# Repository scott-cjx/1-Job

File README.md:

# Overview

`1 Job` is a Custom Designed PCB by [Scott CJX](https://scott-cjx.github.io) for [Nanyang Venture Formula NVF](https://nanyang-venture-formula.github.io/). Since its designer is a software person, `1 Job` is created to follow the principle of programming, having only `1 Job`.

As this PCB is designed to have `1 Job`, you may then wonder what is that `1 Job`. Well it is meant to be one of many nodes in a CanBus network. Its job is to act as either an [Input](#input) or [Output](#output) node. More will be explained.

#### You might want to see:

- [Brain](https://scott-cjx.github.io/brain) - `1 Job's` partner-in-crime
- [NVF-Data Acquisition](https://nanyang-venture-formula.github.io/) - how `1 Job` and `Brain` would work together to form a comprehensive Car EE System.

## Other Documentations

- [Software](./software)
- [Hardware](./hardware)
- [Production](./production)

## Input

An Input node is one that will take in a user input or sensor interface and transmit its reading to the CanBus network. Some sensors that `1 Job` interfaces with include:

- (Analog) Potentiometer
- (Digital) Push Button/ Switch

The standard program flow of an Input node will be as follows:

``` mermaid
flowchart TD
    A[Setup] --> B(Loop)
    B --> C(Read sensor value)
    C --> D(Process sensor value)
    D --> E(Transmit processed \nvalues via CanBus)
    E --> B
```

## Output

An Output node is one that will poll the CanBus network for instructions, pulling a pin high/low as per required. Furthermore, `1 Job` will be equipped with a Solid State Relay, allowing it to connect/ disconnect a circuit much like a programmable switch, but without the need of connecting the circuits together. 

The standard program flow of an Output node will be as follows:

1. Poll for instructions from `brain` nodes
2. Pull pin high/low as per instructed

``` mermaid
flowchart TD
    A[Setup] --> B(Loop)
    B --> C(Wait for CanBus Message)
    C --> D(Read CanBus Instructions)
    D --> E(Drive Pin high/low \nas per instructions)
    E --> B
```

## Preview

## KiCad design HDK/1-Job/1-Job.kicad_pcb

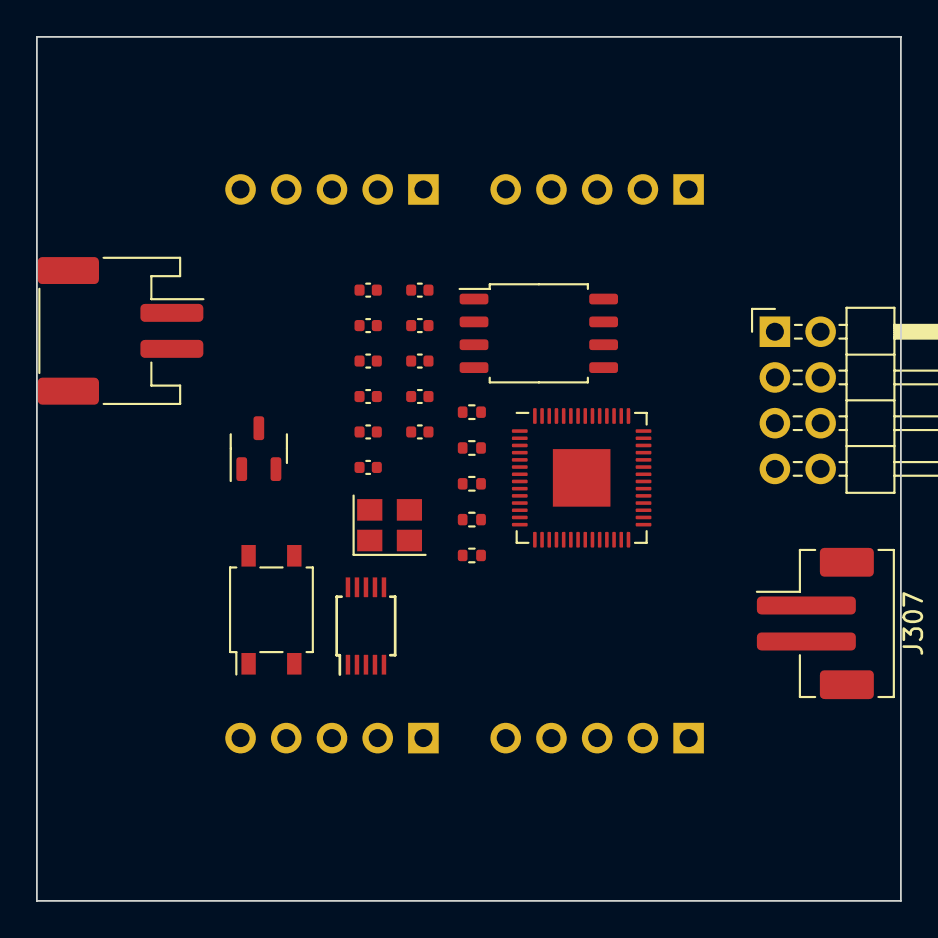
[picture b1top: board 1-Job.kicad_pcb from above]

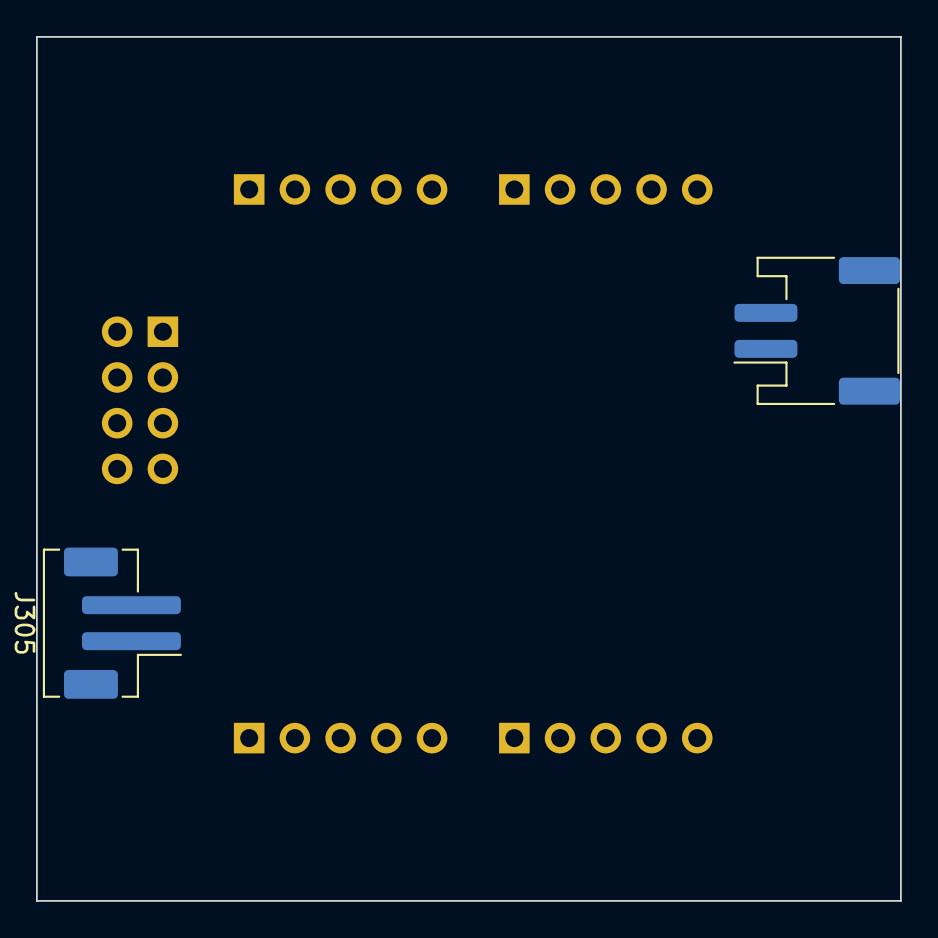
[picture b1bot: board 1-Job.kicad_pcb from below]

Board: 2 copper layers, 48.0 x 48.0 mm, 26 parts (2 on the bottom side), 20 nets, no tracks yet.

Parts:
C201, C202, C203, C204, C205, C206, C207, C208, C209: 100n; C_0402_1005Metric
C210, C211: 10p; C_0402_1005Metric
J301, J303: Can Conn; JST_PH_S2B-PH-SM4-TB_1x02-1MP_P2.00mm_Horizontal
J305, J307: Can Conn; JST_PH_B2B-PH-SM4-TB_1x02-1MP_P2.00mm_Vertical
R201, R205: 1K; R_0402_1005Metric
R202, R203: 27; R_0402_1005Metric
R204: 1K (NC); R_0402_1005Metric
U201: W25Q128JVS; SOIC-8_5.23x5.23mm_P1.27mm
U202: RP2040; QFN-56-1EP_7x7mm_P0.4mm_EP3.2x3.2mm
U401: ADS1015IDGS; TSSOP-10_3x3mm_P0.5mm
U402: ASSR-1218; SO-4_4.4x4.3mm_P2.54mm
U501: LR7533-T LR; SOT-23-3
Y201: 12 MHz; Crystal_SMD_3225-4Pin_3.2x2.5mm

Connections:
+1V1: C208.1, C209.1, U202.23 (DVDD), U202.45 (VREG_VOUT), U202.50 (DVDD)
+3V3: C201.1, C202.1, C203.1, C204.1, C205.1, C206.1, C207.1, R204.1, U201.8 (VCC), U202.1 (IOVDD), U202.10 (IOVDD), U202.22 (IOVDD), U202.33 (IOVDD), U202.42 (IOVDD), U202.43 (ADC_AVDD), U202.44 (VREG_IN), U202.48 (USB_VDD), U202.49 (IOVDD), U401.8 (VDD), U501.2 (VO)
/Connectors/CAN1_H: J301.2, J303.2
/Connectors/CAN1_L: J301.1, J303.1
/Connectors/CAN2_H: J305.2, J307.2
/Connectors/CAN2_L: J305.1, J307.1
/Controller/HSE_IN: C210.1, U202.20 (XIN), Y201.1
/Controller/HSE_OUT: C211.1, R205.1, Y201.3
/Controller/QSPI_SCLK: U201.6 (CLK), U202.52 (QSPI_SCLK)
/Controller/QSPI_SD0: U201.5 (DI(IO0)), U202.53 (QSPI_SD0)
/Controller/QSPI_SD1: U201.2 (DO(IO1)), U202.55 (QSPI_SD1)
/Controller/QSPI_SD2: U201.3 (IO2), U202.54 (QSPI_SD2)
/Controller/QSPI_SD3: U201.7 (IO3), U202.51 (QSPI_SD3)
/Controller/QSPI_SS: R201.1, R204.2, U201.1 (~CS), U202.56 (QSPI_SS)
/I2C0_SCL: U202.12 (GPIO9), U401.10 (SCL)
/I2C0_SDA: U202.11 (GPIO8), U401.9 (SDA)
GND: C201.2, C202.2, C203.2, C204.2, C205.2, C206.2, C207.2, C208.2, C209.2, C210.2, C211.2, U201.4 (GND), U202.19 (TESTEN), U202.57 (GND), U401.1 (ADDR), U401.3 (GND), U402.2, U501.1 (GND), Y201.2, Y201.4
unnamed: R203.2, U202.46 (USB_DM)
unnamed: R202.2, U202.47 (USB_DP)
unnamed: R205.2, U202.21 (XOUT)

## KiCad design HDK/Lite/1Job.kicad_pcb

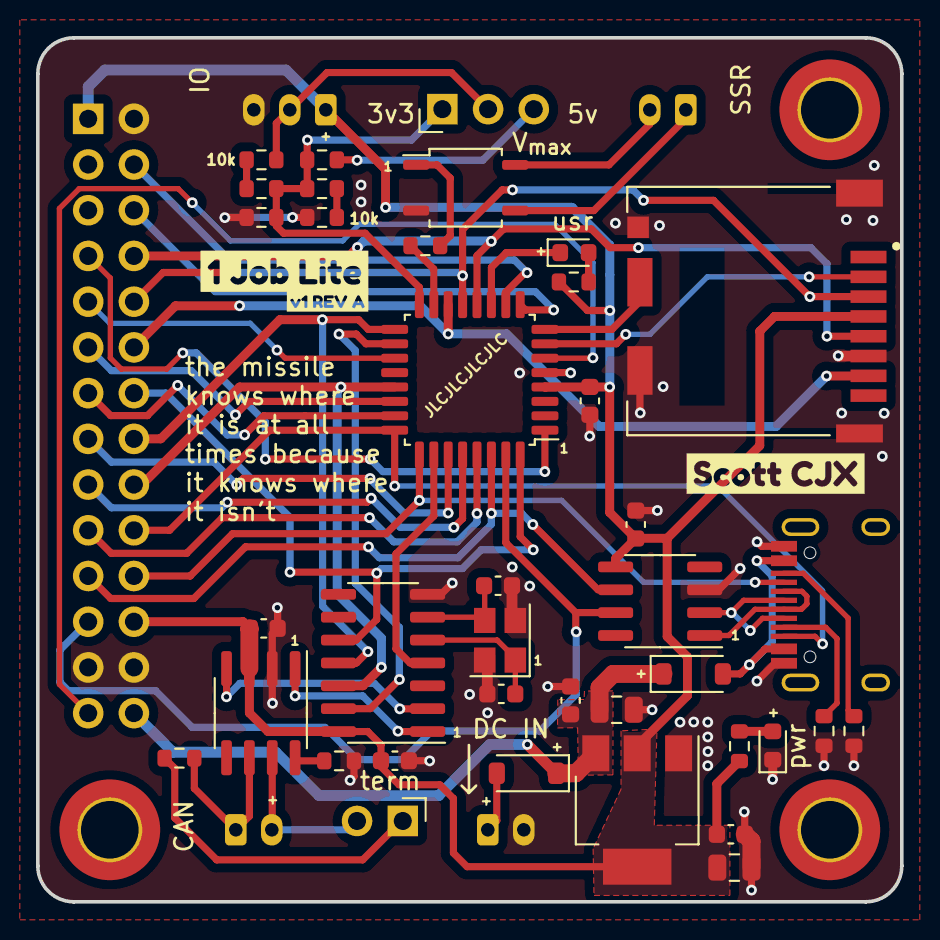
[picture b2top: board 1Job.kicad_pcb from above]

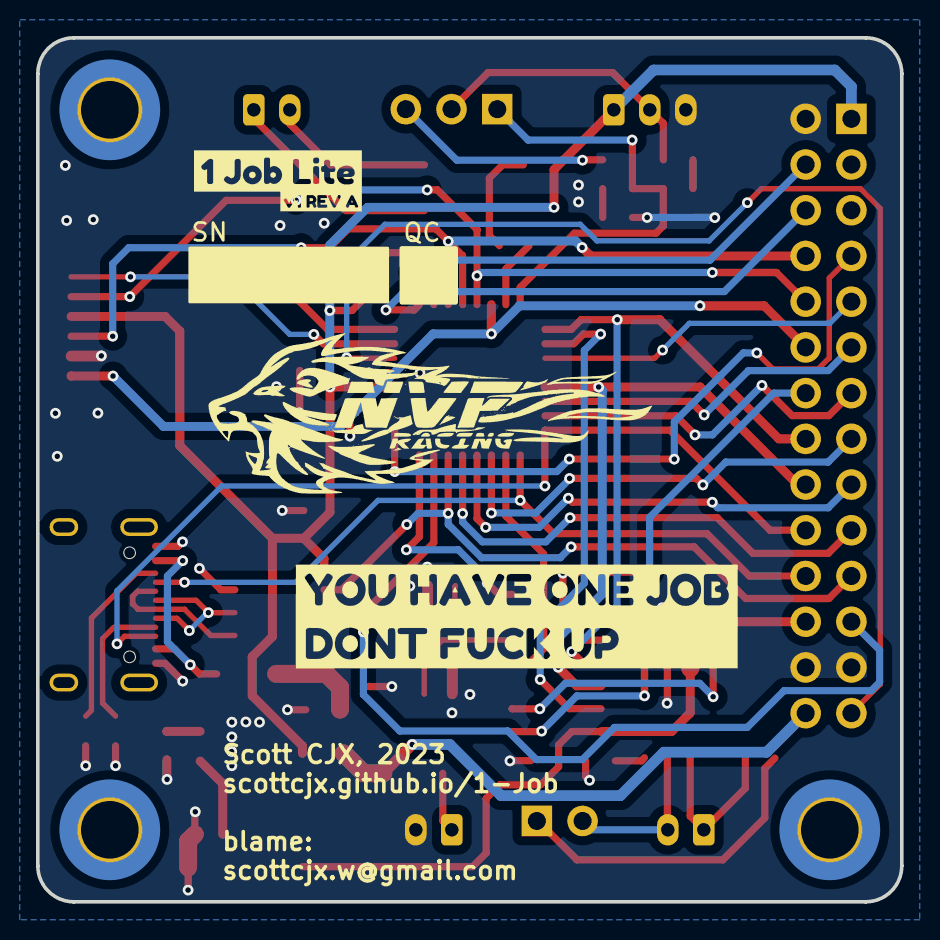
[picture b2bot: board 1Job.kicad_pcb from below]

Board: 2 copper layers, 48.0 x 48.0 mm, 49 parts (3 on the bottom side), 53 nets.

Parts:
C101, C103, C105, C201, C202, C401: 100n; C_0603_1608Metric
C102, C104: 1uF; C_0805_2012Metric
C203, C204: 20p; C_0603_1608Metric
D101, D102: LED; LED_0603_1608Metric
D401, D402: B5819W; D_SOD-123
J201: TERM; PinHeader_1x02_P2.54mm_Horizontal
J302: DM3CS-SF; HRS_DM3CS-SF
J401: SSR; JST-PH-1x02-Horizontal
J402: CAN; JST-PH-1x02-Horizontal
J403: ANA; JST-PH-1x03-Horizontal
J404: PWR; JST-PH-1x02-Horizontal
J405: Conn_02x14_Odd_Even; 48x48 Module
J406: A1-SEL; PinHeader_1x03_P2.54mm_Horizontal
J407: USB C; USB_C_Receptacle_HRO_TYPE-C-31-M-12
R101, R102, R201, R401, R405: 10k; R_0603_1608Metric
R202: 120; R_0603_1608Metric
R402, R403, R404, R406, R408, R409: 5.1k; R_0603_1608Metric
R407: 330; R_0603_1608Metric
U101: STM32G030K6Tx; LQFP-32_7x7mm_P0.8mm
U102: AMS1117-3.3; SOT-223-3_TabPin2
U201: SN65HVD230; SOIC-8_3.9x4.9mm_P1.27mm
U202: MCP2518FD; SOIC-14_3.9x8.7mm_P1.27mm
U401: KAQY214; SOP-4_3.8x4.1mm_P2.54mm
U402: CH340N; SOIC-8_3.9x4.9mm_P1.27mm
Y201: 40MHz; Crystal_SMD_3225-4Pin_3.2x2.5mm
kibuzzard-654FB514: G***; kibuzzard-654FB514
kibuzzard-654FB554, kibuzzard-654FB554#2: G***; kibuzzard-654FB554
kibuzzard-654FB568, kibuzzard-654FB568#2: G***; kibuzzard-654FB568
kibuzzard-6550DE2D: G***; kibuzzard-6550DE2D

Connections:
+3V3: C101.1, C104.1, C105.1, C201.1, C202.1, C401.1, J302.4 (VDD), J403.1, J405.1, J405.24, R101.2, R102.2, U101.4 (VDD), U102.2 (VO), U201.3 (VCC), U202.14 (VDD), U402.5 (VCC)
/1JIO/A1_DIV-05V: J406.3, R404.1
/1JIO/A1_DIV-12V: J403.2, J406.2, R401.1
/1JIO/SSR-IN: J401.2, U401.4
/1JIO/SSR-OUT: J401.1, U401.3
/1JIO/USB_D+: J407.A6 (D+), J407.B6 (D+), U402.1 (UD+)
/1JIO/USB_D-: J407.A7 (D-), J407.B7 (D-), U402.2 (UD-)
/ANA_1: J406.1, R402.2, R403.2, R404.2, R406.2, U101.16 (PB1)
/CAN_+: J201.2, J402.2, U201.7 (CANH)
/CAN_-: J402.1, R202.2, U201.6 (CANL)
/CAN_CS1: U101.18 (PA8), U202.13 (nCS)
/CanBus/CAN_RX: U201.4 (R), U202.2 (RXCAN)
/CanBus/CAN_TX: U201.1 (D), U202.1 (TXCAN)
/CanBus/OSC_IN: C204.1, U202.6 (OSC1), Y201.3
/CanBus/OSC_OUT: C203.1, U202.5 (OSC2), Y201.1
/DO_SSR: R407.1, U101.15 (PB0)
/I2C1_SCL: J405.9, U101.19 (PA9/NC)
/I2C1_SDA: J405.7, U101.1 (PB9)
/I2C2_SCL: J405.13, U101.23 (PA12/PA10)
/I2C2_SDA: J405.11, U101.22 (PA11/PA9)
/PA0: J302.2 (CD/DAT3), U101.7 (PA0)
/PA1: J302.9 (CD_SW), U101.8 (PA1)
/PA2: J405.6, U101.9 (PA2)
/PA3: J405.4, U101.10 (PA3)
/PA4: D101.1 (K), U101.11 (PA4)
/PA5: J302.5 (CLK), J405.8, U101.12 (PA5)
/PA6: J302.3 (CMD), J405.10, U101.13 (PA6)
/PA7: J302.7 (DAT0), J405.12, U101.14 (PA7)
/PA10: J405.18, U101.21 (PA10/NC), U202.12 (SDO)
/PA13: J405.20, J407.B8 (SBU2), U101.24 (PA13)
/PA14: J405.22, J407.A8 (SBU1), U101.25 (PA14)
/PA15: U101.26 (PA15), U202.4 (~INT)
/PB2: J405.16, U101.17 (PB2), U202.11 (SDI)
/PB3: J405.15, U101.27 (PB3)
/PB4: J405.17, U101.28 (PB4)
/PB5: J405.19, U101.29 (PB5)
/PB6: J405.21, U101.30 (PB6), U402.6 (TXD)
/PB7: J405.23, U101.31 (PB7), U402.7 (RXD)
/PB8: J405.14, U101.32 (PB8), U202.10 (SCK)
/~NRST: J405.27, U101.6 (NRST)
GND: C101.2, C102.2, C103.2, C104.2, C105.2, C201.2, C202.2, C203.2, C204.2, C401.2, D102.1 (K), J302.6 (VSS), J302.S1 (GND), J302.S2 (GND), J302.S3 (GND), J302.S5 (GND), J403.3, J404.2, J405.2, J405.25, J405.26, J407.A1 (GND), J407.A12 (GND), J407.B1 (GND), J407.B12 (GND), R201.1, R403.1, R405.1, R408.2, R409.2, U101.5 (VSS), U102.1 (GND), U201.2 (GND), U202.7 (VSS), U401.2, U402.3 (GND), Y201.2, Y201.4
unnamed: D101.2 (A), R101.1
unnamed: D102.2 (A), R102.1
unnamed: D401.2 (A), J404.1
unnamed: J201.1, R202.1
unnamed: J407.A5 (CC1), R408.1
unnamed: J407.B5 (CC2), R409.1
unnamed: R401.2, R402.1
unnamed: R405.2, R406.1
unnamed: R407.2, U401.1
unnamed: R201.2, U201.8 (Rs)
VBUS: D402.2 (A), J407.A4 (VBUS), J407.A9 (VBUS), J407.B4 (VBUS), J407.B9 (VBUS)
VCC: C102.1, C103.1, D401.1 (K), D402.1 (K), J405.28, U102.3 (VI)

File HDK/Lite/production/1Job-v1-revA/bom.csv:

Designator,Footprint,Quantity,Value,LCSC Part #
"C101, C103, C105, C201, C202, C401",0603,6,100n,C57112
"C102, C104",0805,2,1uF,C28323
"C203, C204",0603,2,20p,C1648
"D101, D102",0603,2,LED,C2286
"D401, D402",D_SOD-123,2,B5819W,C8598
J201,PinHeader_1x02_P2.54mm_Horizontal,1,TERM,
J302,HRS_DM3CS-SF,1,DM3CS-SF,
J401,JST-PH-1x02-Horizontal,1,SSR,C173752
J402,JST-PH-1x02-Horizontal,1,CAN,C173752
J403,JST-PH-1x03-Horizontal,1,ANA,C157929
J404,JST-PH-1x02-Horizontal,1,PWR,C173752
J405,48x48 Module,1,Conn_02x14_Odd_Even,
J406,PinHeader_1x03_P2.54mm_Horizontal,1,A1-SEL,
J407,USB_C_Receptacle_HRO_TYPE-C-31-M-12,1,USB C,C165948
"R101, R102, R201, R401, R405",0603,5,10k,C25804
R202,0603,1,120,C22787
"R402, R403, R404, R406, R408, R409",0603,6,5.1k,0603
R407,0603,1,330,C23138
U101,LQFP-32_7x7mm_P0.8mm,1,STM32G030K6Tx,C724043
U102,SOT-223-3_TabPin2,1,AMS1117-3.3,C6186
U201,SOIC-8_3.9x4.9mm_P1.27mm,1,SN65HVD230,C12084
U202,SOIC-14_3.9x8.7mm_P1.27mm,1,MCP2518FD,C626758
U401,SOP-4_3.8x4.1mm_P2.54mm,1,KAQY214,C113331
U402,SOIC-8_3.9x4.9mm_P1.27mm,1,CH340N,C2977777
Y201,Crystal_SMD_3225-4Pin_3.2x2.5mm,1,40MHz,C9010

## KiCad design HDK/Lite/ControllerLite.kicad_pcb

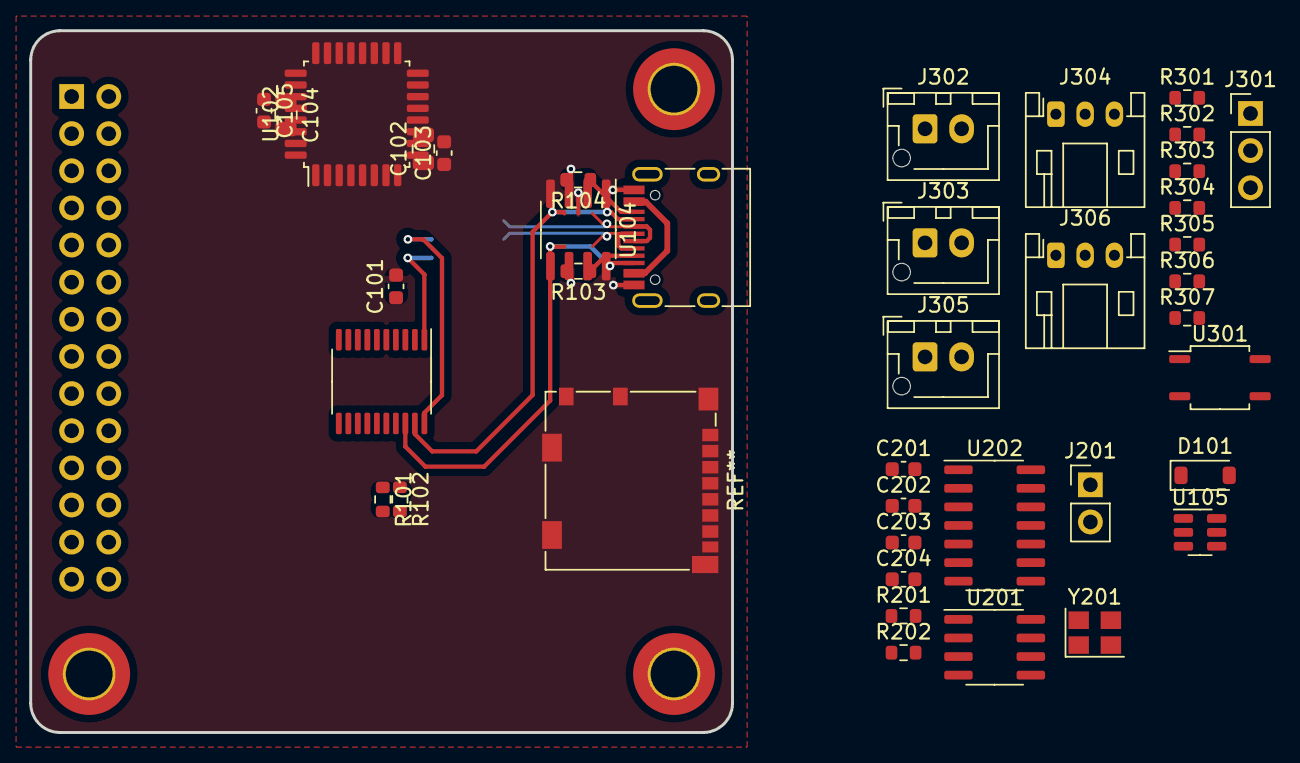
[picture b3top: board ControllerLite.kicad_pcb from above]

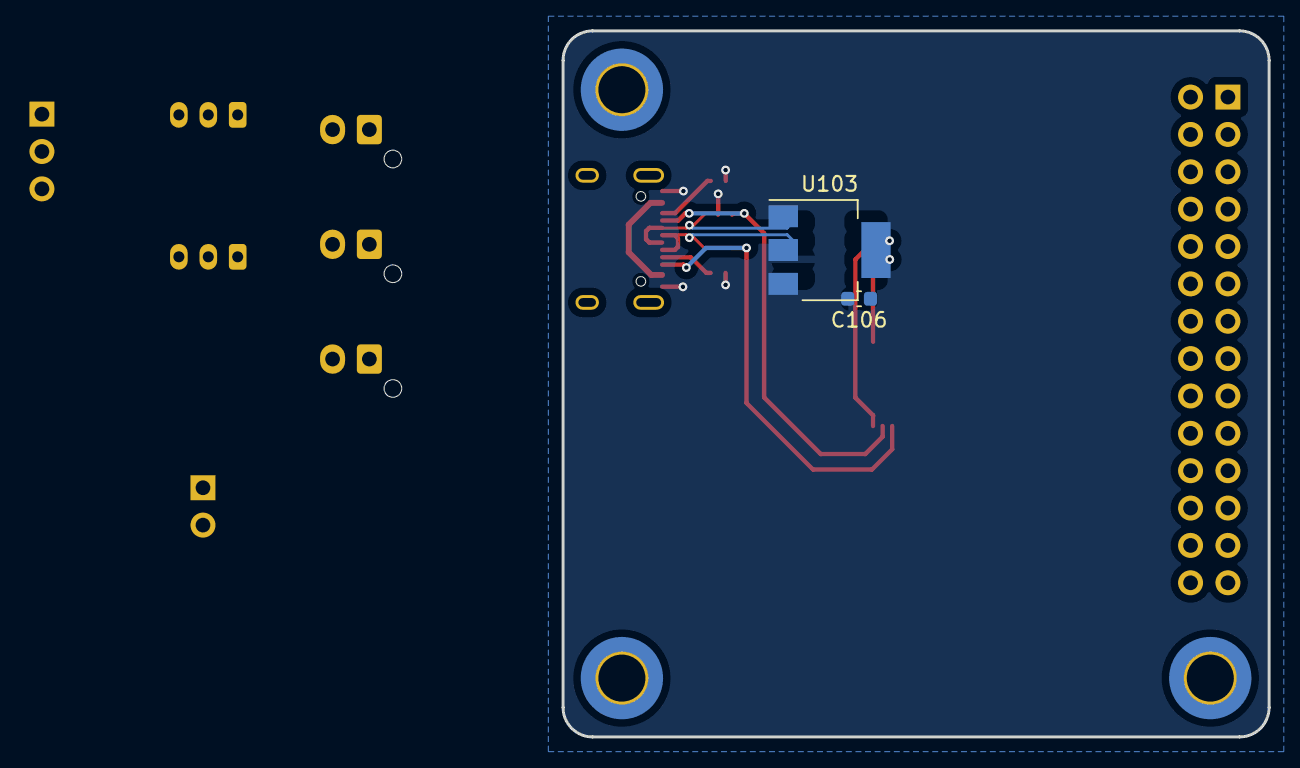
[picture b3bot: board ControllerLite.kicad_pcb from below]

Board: 2 copper layers, 48.0 x 48.0 mm, 41 parts (2 on the bottom side), 28 nets.

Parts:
C101, C103, C105, C106, C201, C202: 100n; C_0603_1608Metric
C102, C104: 1uF; C_0805_2012Metric
C203, C204: 10p; C_0603_1608Metric
D101: 1N4148W; D_SOD-123
J101: USB C; USB_C_Receptacle_HRO_TYPE-C-31-M-12
J201: TERM; PinHeader_1x02_P2.54mm_Vertical
J301: A1-SEL; PinHeader_1x03_P2.54mm_Vertical
J302: SSR; JST_XH_B2B-XH-AM_1x02_P2.50mm_Vertical
J303: CAN; JST_XH_B2B-XH-AM_1x02_P2.50mm_Vertical
J304: ANA; JST_PH_S3B-PH-K_1x03_P2.00mm_Horizontal
J305: PWR; JST_XH_B2B-XH-AM_1x02_P2.50mm_Vertical
J306: DIO; JST_PH_S3B-PH-K_1x03_P2.00mm_Horizontal
R101, R102, R103, R104, R302, R303, R304, R306: 5.1k; R_0603_1608Metric
R201, R301, R305: 10k; R_0603_1608Metric
R202: 120; R_0603_1608Metric
R307: 330; R_0603_1608Metric
U101: STM32G030F6Px; TSSOP-20_4.4x6.5mm_P0.65mm
U102: STM32G030K6Tx; LQFP-32_7x7mm_P0.8mm
U103: AMS1117-3.3; SOT-223-3_TabPin2
U104: CH340N; SOIC-8_3.9x4.9mm_P1.27mm
U105: USBLC6-4SC6; SOT-23-6
U201: SN65HVD230; SOIC-8_3.9x4.9mm_P1.27mm
U202: MCP2518FD; SOIC-14_3.9x8.7mm_P1.27mm
U301: KAQY214; SOP-4_3.8x4.1mm_P2.54mm
Y201: 40MHz; Crystal_SMD_3225-4Pin_3.2x2.5mm

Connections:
+3V3: C101.1, C104.1, C105.1, C106.1, C201.1, C202.1, J304.1, J306.1, R101.2, R102.2, U101.4 (VDD), U103.2 (VO), U104.5 (VCC), U201.3 (VCC), U202.14 (VDD)
/1JIO/A1_DIV-03V: J301.1, J304.2, R301.1, R304.1
/1JIO/A1_DIV-05V: J301.3, R304.2, R306.2
/1JIO/A1_DIV-12V: J301.2, R302.2, R303.2
/1JIO/SSR-IN: J302.1, U301.4
/1JIO/SSR-OUT: J302.2, U301.3
/CanBus/CAN_+: J201.1, U201.7 (CANH)
/CanBus/CAN_-: R202.2, U201.6 (CANL)
/CanBus/CAN_RX: U201.4 (R), U202.2 (RXCAN)
/CanBus/CAN_TX: U201.1 (D), U202.1 (TXCAN)
/CanBus/OSC_IN: C204.1, U202.6 (OSC1), Y201.4
/CanBus/OSC_OUT: C203.1, U202.5 (OSC2), Y201.1
/I2C_SCL: R101.1, U101.16 (PA11/PA9)
/I2C_SDA: R102.1, U101.17 (PA12/PA10)
/SWCLK: J101.A8 (SBU1), U101.19 (PA14/PA15), U105.3 (I/O2)
/SWDIO: J101.B8 (SBU2), U101.18 (PA13), U105.4 (I/O3)
/USB_D+: J101.A6 (D+), J101.B6 (D+), U104.1 (UD+), U105.1 (I/O1)
/USB_D-: J101.A7 (D-), J101.B7 (D-), U104.2 (UD-), U105.6 (I/O4)
GND: C101.2, C102.2, C103.2, C104.2, C105.2, C106.2, C201.2, C202.2, C203.2, C204.2, J101.A1 (GND), J101.A12 (GND), J101.B1 (GND), J101.B12 (GND), J304.3, J305.2, J306.3, R103.2, R104.2, R201.1, R303.1, R305.1, U101.5 (VSS), U103.1 (GND), U104.3 (GND), U105.2 (GND), U201.2 (GND), U202.7 (VSS), U301.2, Y201.2, Y201.3
unnamed: J101.A5 (CC1), R103.1
unnamed: J101.B5 (CC2), R104.1
unnamed: J201.2, R202.1
unnamed: R301.2, R302.1
unnamed: R305.2, R306.1
unnamed: R307.2, U301.1
unnamed: R201.2, U201.8 (Rs)
VBUS: D101.2 (A), J101.A4 (VBUS), J101.A9 (VBUS), J101.B4 (VBUS), J101.B9 (VBUS)
VCC: C102.1, C103.1, D101.1 (K), U103.3 (VI)

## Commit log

2023-11-09 Initialize gh-pages
2023-11-09 Moving files docs/* LICENSE using main
2023-11-09 Deploying to gh-pages from @ scott-cjx/1-Job-Lite@64dc98748d275c28064337cf29281841178e9bdb 🚀
2023-11-09 added schematics
2023-11-09 Deploying to gh-pages from @ scott-cjx/1-Job@35ebab82509c08bb62a31fb405485a8da5ff6666 🚀
2023-11-09 Deploying to gh-pages from @ scott-cjx/1-Job@eb947d95f914f3daf9dd5a802b8fbd736e5fb2cc 🚀
2023-11-09 Deploying to gh-pages from @ scott-cjx/1-Job@065a27a0329548bae73877d699f667bff2f71241 🚀
2023-11-09 updated docs
2023-11-09 Deploying to gh-pages from @ scott-cjx/1-Job@c8c29ba1e56d47fca471c2fc5d306ed2a8cca76b 🚀
2023-11-09 Deploying to gh-pages from @ scott-cjx/1-Job@3bee38ff9a2b7fb698491f2e16bb7d2da20b55c8 🚀
2023-11-09 added render-mermaid action
2023-11-09 Deploying to gh-pages from @ scott-cjx/1-Job@2f5b75381fdcb657782a21bdbc960f1123bab992 🚀
2023-11-09 Deploying to gh-pages from @ scott-cjx/1-Job@3df732c5c5e711a89b3c4f897385267c58e2ff70 🚀
2023-11-09 Deploying to gh-pages from @ scott-cjx/1-Job@a73a918c8cf4ca71ea932231ca7caae50a96f4d9 🚀
2023-11-09 Deploying to gh-pages from @ scott-cjx/1-Job@6889699f8571af484b60e879b5ba4fde695f19f8 🚀
2023-11-09 Deploying to gh-pages from @ scott-cjx/1-Job@28748df800954df5750bcfb33b7dbd8f5114b6ca 🚀
2023-11-09 Deploying to gh-pages from @ scott-cjx/1-Job@32baa5e80bbe187cba35fd00bc8bef14ba1f8ff0 🚀
2023-11-10 updated 1 Job
2023-11-10 Deploying to gh-pages from @ scott-cjx/1-Job@2c5c18c946399ad9d501c617b77de969ea2b35c1 🚀
2023-11-10 updated 1 Job, WIP
2023-11-10 Deploying to gh-pages from @ scott-cjx/1-Job@2dca5b7470a0ed2a04e704badff2769e0a8342ce 🚀
2023-11-10 added SDK, WIP
2023-11-10 todo: connect SD_DET
2023-11-10 Deploying to gh-pages from @ scott-cjx/1-Job@6f4e8984599f9eeef056d7334f8e6b5965eeea21 🚀
2023-11-11 updated 1Job, 75%
2023-11-11 Deploying to gh-pages from @ scott-cjx/1-Job@7be7088b8c8d732188496c4a506fa34b921396f6 🚀
2023-11-11 updated 1 Job, 85%
2023-11-11 Deploying to gh-pages from @ scott-cjx/1-Job@1c56f85463eb6844ca37fa3ae69a4bab145dfd79 🚀
2023-11-11 added ibom to rsc
2023-11-11 Deploying to gh-pages from @ scott-cjx/1-Job@b98bae454366d06198dd22d197a5d7b68a7f43dd 🚀
2023-11-12 updated 1-Job, v1rA
2023-11-12 Deploying to gh-pages from @ scott-cjx/1-Job@f8994db3b9dc069d9317b0fdbbd5e734eea9c235 🚀
2023-11-12 added preview to docs
2023-11-12 Deploying to gh-pages from @ scott-cjx/1-Job@83107f7e12720c2200dc40e45e8b233a1a77727d 🚀
2023-11-12 updated 1job silkscreen
2023-11-13 Deploying to gh-pages from @ scott-cjx/1-Job@e6f5bf083daf48239aee02e309f6a02e7ad18b1e 🚀
2023-11-14 updated 1job
2023-11-14 Deploying to gh-pages from @ scott-cjx/1-Job@2719ab5c47c7c5a0a81e4d506bca6766660f5723 🚀
2023-11-14 updated renders
2023-11-14 Deploying to gh-pages from @ scott-cjx/1-Job@1068c9a76bef0a1b3fa40001821e3ae4ca8102b4 🚀
2023-11-14 updated BOM, wip
2023-11-14 Deploying to gh-pages from @ scott-cjx/1-Job@5affd4a22977c9cb924674b5912d7d48a1c53bae 🚀
2023-11-15 Deploying to gh-pages from @ scott-cjx/1-Job@4401b198b4cbb1a93689633dd54da02fed8e8bb5 🚀
2023-11-15 Deploying to gh-pages from @ scott-cjx/1-Job@f19db98e164ad684722b7fc676ef08475e1ee00f 🚀
2023-12-20 init v2
